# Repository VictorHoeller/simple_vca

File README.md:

# simple_vca

This is a very simple dual VCA with CV input, audio input and audio output. Both very simple twice identical next to each other. It has a trimmer to adjust the "no volume".

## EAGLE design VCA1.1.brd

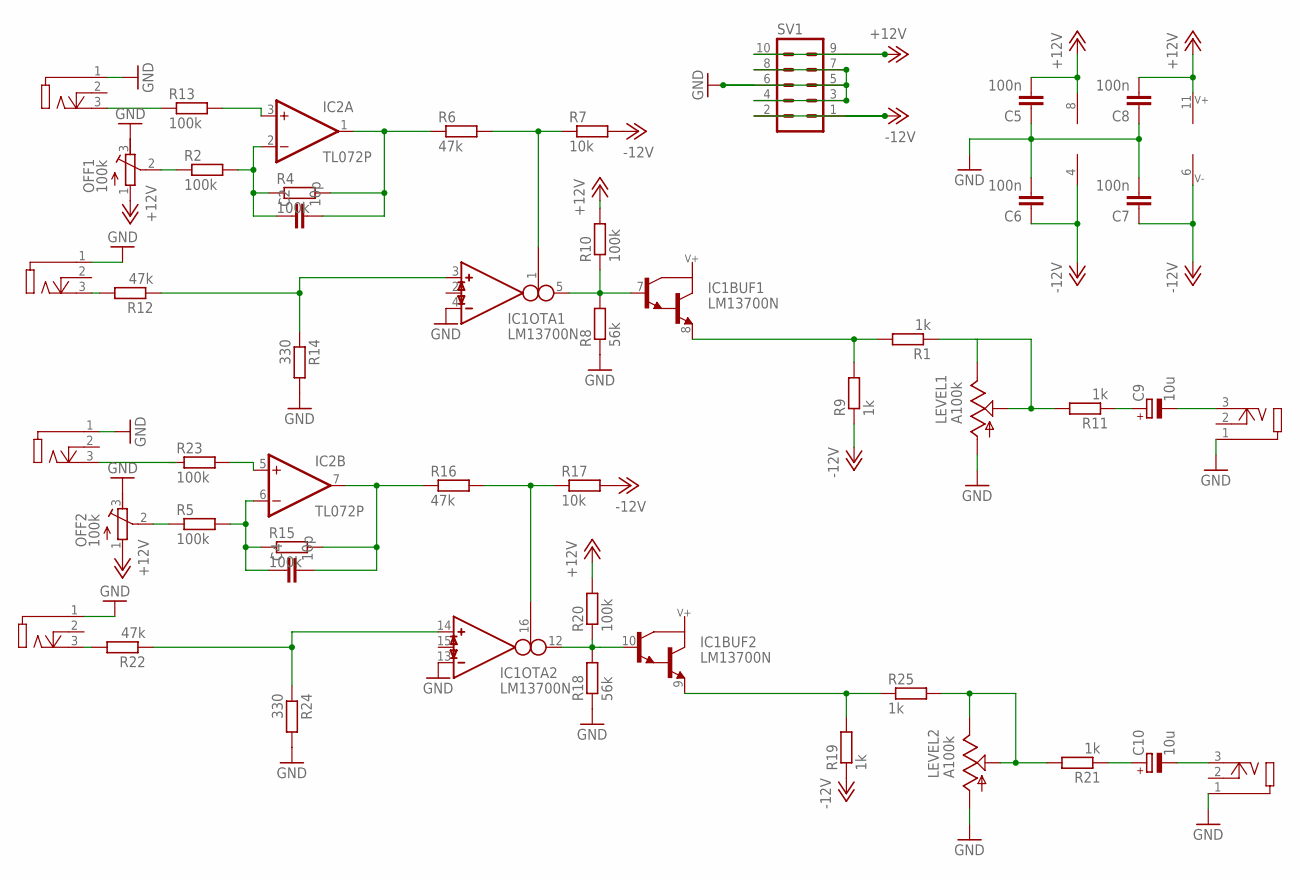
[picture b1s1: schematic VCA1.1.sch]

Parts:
C2, C4: 10p; C025-024X044
C5, C6, C7, C8: 100n; C025-024X044
C9, C10: 10u; E2,5-6E
CV1, CV2: 3.5MM_MONO_SWITCH_VERT; PJ398SM
IC1: LM13700N; DIL16
IC2: TL072P; DIL08
IN1, IN2: 3.5MM_MONO_SWITCH_VERT; PJ398SM
LEVEL1, LEVEL2: A100k; PTV09
OFF1, OFF2: 100k; RTRIM3296X
OUT1, OUT2: 3.5MM_MONO_SWITCH_VERT; PJ398SM
R1, R9, R11, R19, R21, R25: 1k; 0204/7
R2, R4, R5, R10, R13, R15, R20, R23: 100k; 0204/7
R6, R12, R16, R22: 47k; 0204/7
R7, R17: 10k; 0204/7
R8, R18: 56k; 0204/7
R14, R24: 330; 0204/7
SV1: ML10

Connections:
+12V: C5.2, C8.2, IC1.11 (V+), IC2.8 (V+), OFF1.1 (A), OFF2.1 (A), R10.2, R20.2, SV1.9, SV1.10
-12V: C6.1, C7.1, IC1.6 (V-), IC2.4 (V-), R7.2, R9.1, R17.2, R19.1, SV1.1, SV1.2
GND: C5.1, C6.2, C7.2, C8.1, CV1.1, CV2.1, IC1.4 (IN_N), IC1.13 (IN_N), IN1.1, IN2.1, LEVEL1.1 (A), LEVEL2.1 (A), OFF1.3 (E), OFF2.3 (E), OUT1.1, OUT2.1, R8.1, R14.2, R18.1, R24.2, SV1.3, SV1.4, SV1.5, SV1.6, SV1.7, SV1.8
unnamed: C2.1, IC2.2 (-IN), R2.2, R4.1
unnamed: IC2.3 (+IN), R13.2
unnamed: IC1.3 (IN_P), R12.1, R14.1
unnamed: C2.2, IC2.1 (OUT), R4.2, R6.1
unnamed: OFF1.2 (S), R2.1
unnamed: IC1.1 (I_BIAS), R6.2, R7.1
unnamed: IC1.5 (OUT), IC1.7 (B), R8.2, R10.1
unnamed: IN1.3, R12.2
unnamed: CV1.3, R13.1
unnamed: C4.1, IC2.6 (-IN), R5.2, R15.1
unnamed: IC1.8 (E), R1.2, R9.2
unnamed: LEVEL1.2 (S), LEVEL1.3 (E), R1.1, R11.2
unnamed: C9.+, R11.1
unnamed: C9.-, OUT1.3
unnamed: C4.2, IC2.7 (OUT), R15.2, R16.1
unnamed: IC1.16 (I_BIAS), R16.2, R17.1
unnamed: IC1.10 (B), IC1.12 (OUT), R18.2, R20.1
unnamed: IN2.3, R22.2
unnamed: IC1.9 (E), R19.2, R25.1
unnamed: LEVEL2.2 (S), LEVEL2.3 (E), R21.2, R25.2
unnamed: C10.+, R21.1
unnamed: C10.-, OUT2.3
unnamed: OFF2.2 (S), R5.1
unnamed: CV2.3, R23.1
unnamed: IC2.5 (+IN), R23.2
unnamed: IC1.14 (IN_P), R22.1, R24.1

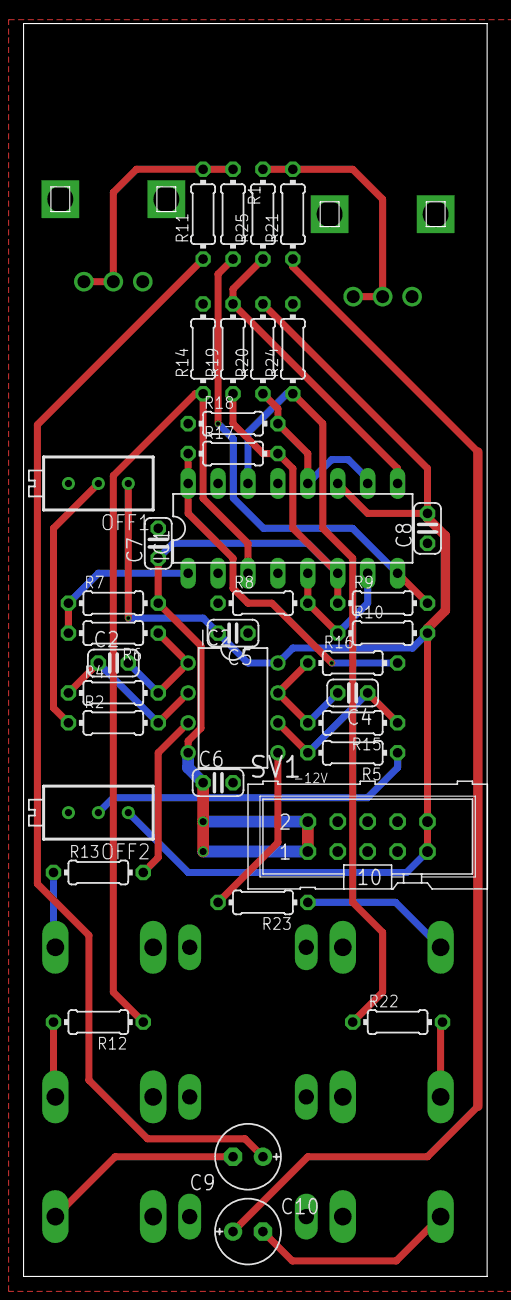
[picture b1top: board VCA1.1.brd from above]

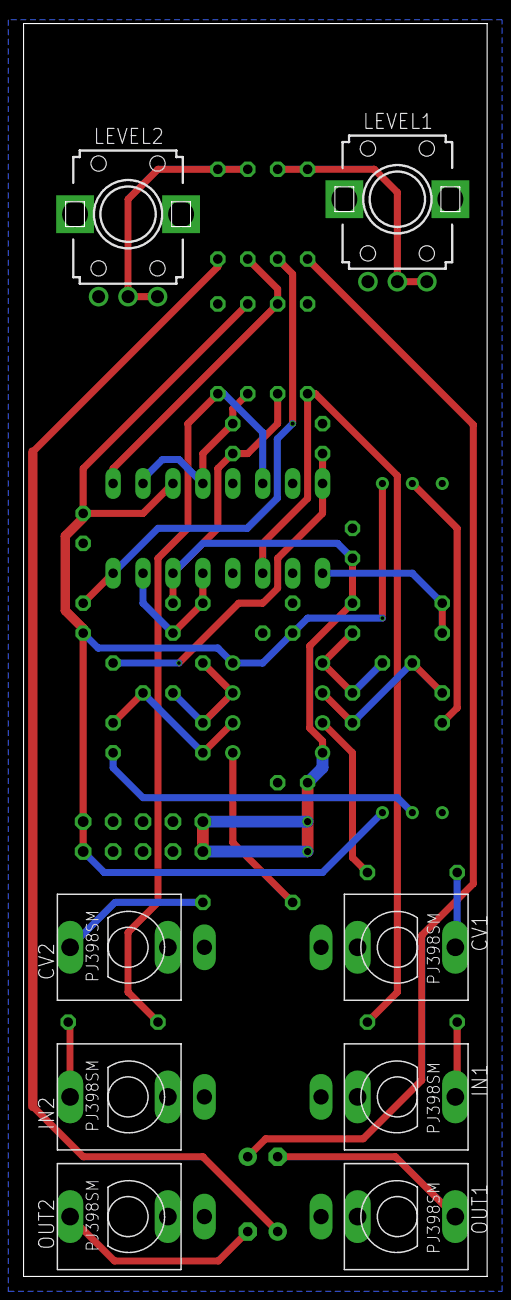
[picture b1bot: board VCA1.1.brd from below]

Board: 2 copper layers, 39.4 x 106.3 mm, 45 parts (8 on the bottom side), 29 nets.
